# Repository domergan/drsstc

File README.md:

# Dual Resonance SSTC

My repo containing all my files and codes for my DRSSTC project. 

## Sources

- https://www.stevehv.4hv.org/DRSSTC.5.htm
- https://www.stevehv.4hv.org/new_driver.html
- https://www.f-legrand.fr/scidoc/docmml/sciphys/arduino/onduleur2/onduleur2.html

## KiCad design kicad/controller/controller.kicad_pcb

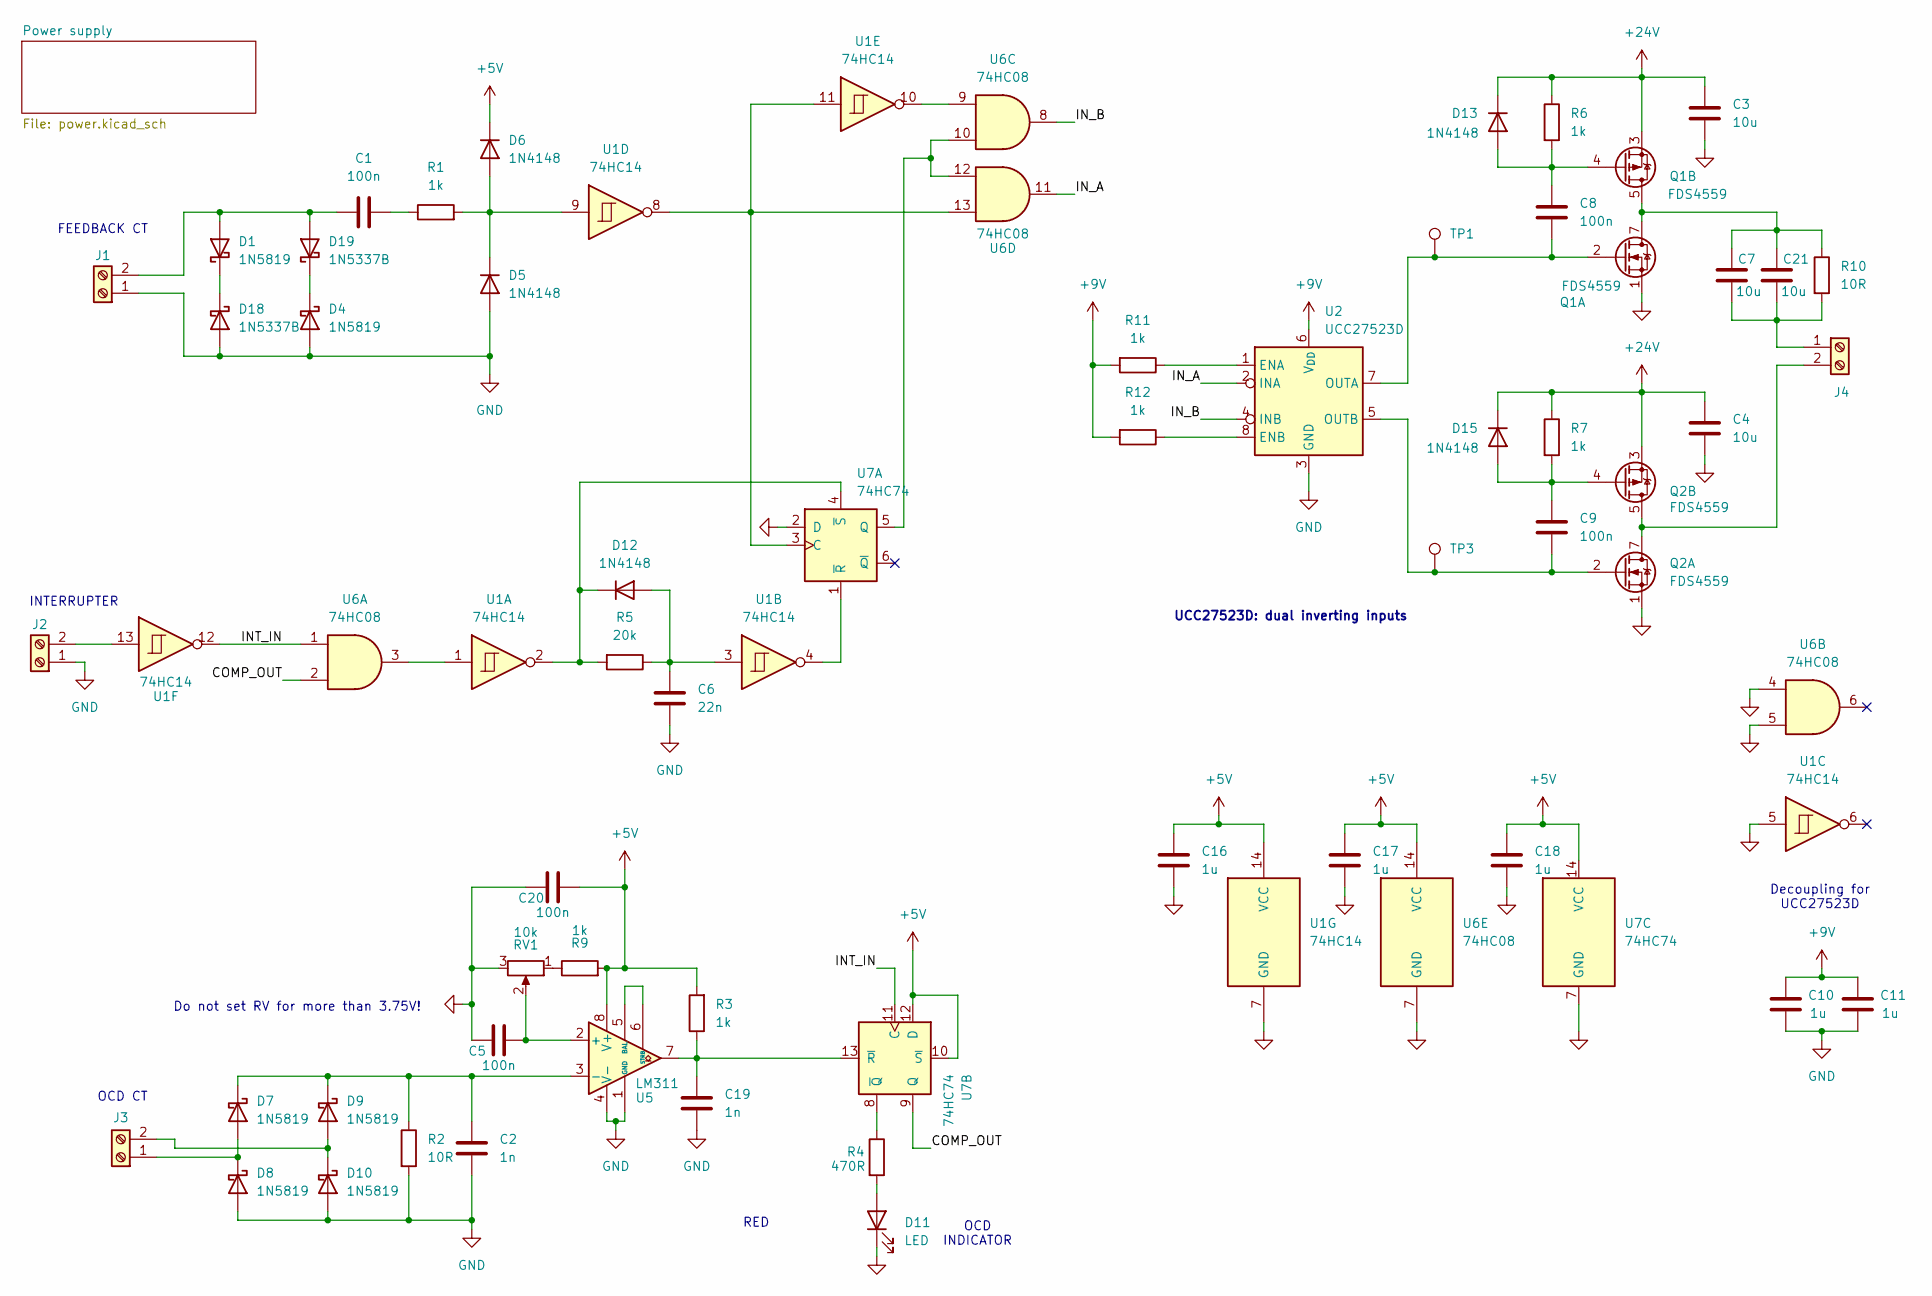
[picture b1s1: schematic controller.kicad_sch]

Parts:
C1, C5, C8, C9, C20: 100n; C_0805_2012Metric_Pad1.18x1.45mm_HandSolder
C2, C19: 1n; C_0805_2012Metric_Pad1.18x1.45mm_HandSolder
C3, C4, C7, C21: 10u; C_1206_3216Metric_Pad1.33x1.80mm_HandSolder
C6: 22n; C_0805_2012Metric_Pad1.18x1.45mm_HandSolder
C10, C11, C17, C18: 1u; C_1206_3216Metric_Pad1.33x1.80mm_HandSolder
C16: 1u; C_1206_3216Metric_Pad1.33x1.80mm_HandSolder; Voltage 10V
D1, D4, D7, D8, D9, D10: 1N5819; D_DO-41_SOD81_P2.54mm_Vertical_CathodeUp
D5, D6, D12, D13, D15: 1N4148; D_DO-35_SOD27_P2.54mm_Vertical_CathodeUp
D11: LED; LED_D3.0mm
D18, D19: 1N5337B; D_DO-201AD_P12.70mm_Horizontal
J1, J2, J3, J4: Screw_Terminal_01x02; TerminalBlock_MaiXu_MX126-5.0-02P_1x02_P5.00mm
Q1, Q2: FDS4559; SOIC-8_3.9x4.9mm_P1.27mm
R1, R3, R6, R7, R9, R11, R12: 1k; R_0805_2012Metric_Pad1.20x1.40mm_HandSolder
R2, R10: 10R; R_1206_3216Metric_Pad1.30x1.75mm_HandSolder
R4: 470R; R_0805_2012Metric_Pad1.20x1.40mm_HandSolder
R5: 20k; R_0805_2012Metric_Pad1.20x1.40mm_HandSolder
RV1: 10k; Potentiometer_Bourns_3266Y_Vertical
TP1, TP3: TestPoint; TestPoint_THTPad_D2.0mm_Drill1.0mm
U1: 74HC14; SOIC-14_3.9x8.7mm_P1.27mm
U2: UCC27523D; SOIC-8_3.9x4.9mm_P1.27mm
U5: LM311; SOIC-8_3.9x4.9mm_P1.27mm
U6: 74HC08; SOIC-14_3.9x8.7mm_P1.27mm
U7: 74HC74; SOIC-14_3.9x8.7mm_P1.27mm

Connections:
+5V: C16.2, C17.2, C18.2, C20.1, D6.1 (K), R3.2, R9.2, U1.14 (VCC), U5.8 (V+), U6.14 (VCC), U7.10 (~S), U7.12 (D), U7.14 (VCC); also elsewhere on the board
+9V: C10.2, C11.2, R11.2, R12.2, U2.6 (V_{DD}); also elsewhere on the board
+24V: C3.2, C4.2, D13.1 (K), D15.1 (K), Q1.3 (S2), Q2.3 (S2), R6.1, R7.1; also elsewhere on the board
/COMP_OUT: U6.2, U7.9 (Q)
/INT_IN: U1.12, U6.1, U7.11 (C)
/IN_A: U2.2 (INA), U6.11
/IN_B: U2.4 (INB), U6.8
GND: C2.1, C3.1, C4.1, C5.2, C6.2, C10.1, C11.1, C16.1, C17.1, C18.1, C19.2, C20.2, D4.2 (A), D5.2 (A), D8.2 (A), D10.2 (A), D11.1 (K), D18.2 (A), J1.1, J2.1, Q1.1 (S1), Q2.1 (S1), R2.2, RV1.3, U1.5, U1.7 (GND), U2.3 (GND), U5.1 (GND), U5.4 (V-), U6.4, U6.5, U6.7 (GND), U7.2 (D), U7.7 (GND); also elsewhere on the board
unnamed: C1.2, R1.1
unnamed: C7.2, C21.2, Q1.5 (D2), Q1.6 (D2), Q1.7 (D1), Q1.8 (D1), R10.1
unnamed: C1.1, D1.2 (A), D19.2 (A), J1.2
unnamed: D1.1 (K), D18.1 (K)
unnamed: D5.1 (K), D6.2 (A), R1.2, U1.9
unnamed: D7.2 (A), D8.1 (K), J3.1
unnamed: C2.2, D7.1 (K), D9.1 (K), R2.1, U5.3 (-)
unnamed: D9.2 (A), D10.1 (K), J3.2
unnamed: D11.2 (A), R4.2
unnamed: C6.1, D12.2 (A), R5.1, U1.3
unnamed: D12.1 (K), R5.2, U1.2, U7.4 (~S)
unnamed: C8.1, D13.2 (A), Q1.4 (G2), R6.2
unnamed: C9.1, D15.2 (A), Q2.4 (G2), R7.2
unnamed: D4.1 (K), D19.1 (K)
unnamed: J2.2, U1.13
unnamed: C7.1, C21.1, J4.1, R10.2
unnamed: J4.2, Q2.5 (D2), Q2.6 (D2), Q2.7 (D1), Q2.8 (D1)
unnamed: C8.2, Q1.2 (G1), TP1.1 (1_1), U2.7 (OUTA)
unnamed: C9.2, Q2.2 (G1), TP3.1 (1_1), U2.5 (OUTB)
unnamed: R9.1, RV1.1
unnamed: U1.1, U6.3
unnamed: U1.10, U6.9
unnamed: R11.1, U2.1 (ENA)
unnamed: R12.1, U2.8 (ENB)
unnamed: C5.1, RV1.2, U5.2 (+)
unnamed: U5.5 (BAL), U5.6 (STRB)
unnamed: U1.8, U1.11, U6.13, U7.3 (C)
unnamed: U6.10, U6.12, U7.5 (Q)
unnamed: U1.4, U7.1 (~R)
unnamed: R4.1, U7.8 (~Q)
unnamed: C19.1, R3.1, U5.7, U7.13 (~R)

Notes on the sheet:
OCD INDICATOR
Decoupling for UCC27523D
INTERRUPTER
UCC27523D: dual inverting inputs
FEEDBACK CT
OCD CT
Do not set RV for more than 3.75V!
RED

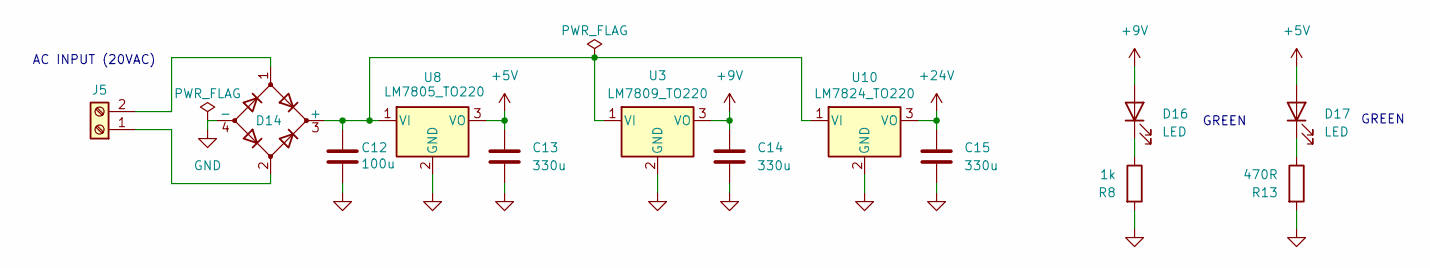
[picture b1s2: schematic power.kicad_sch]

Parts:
C12: 100u; CP_Radial_D10.0mm_P5.00mm
C13, C14, C15: 330u; CP_Radial_D10.0mm_P5.00mm
D14: TB210S; TB210S_ABS
D16, D17: LED; LED_D3.0mm
J5: Screw_Terminal_01x02; TerminalBlock_MaiXu_MX126-5.0-02P_1x02_P5.00mm
R8: 1k; R_0805_2012Metric_Pad1.20x1.40mm_HandSolder
R13: 470R; R_0805_2012Metric_Pad1.20x1.40mm_HandSolder
U3: LM7809_TO220; TO-220-3_Vertical
U8: LM7805_TO220; TO-220-3_Vertical
U10: LM7824_TO220; TO-220-3_Vertical

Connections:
+5V: C13.1, D17.2 (A), U8.3 (VO); also elsewhere on the board
+9V: C14.1, D16.2 (A), U3.3 (VO); also elsewhere on the board
+24V: C15.1, U10.3 (VO); also elsewhere on the board
GND: C12.2, C13.2, C14.2, C15.2, D14.4 (-), R8.2, R13.2, U3.2 (GND), U8.2 (GND), U10.2 (GND); also elsewhere on the board
unnamed: C12.1, D14.3 (+), U3.1 (VI), U8.1 (VI), U10.1 (VI)
unnamed: D16.1 (K), R8.1
unnamed: D17.1 (K), R13.1
unnamed: D14.2, J5.1
unnamed: D14.1, J5.2

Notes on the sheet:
AC INPUT (20VAC)
GREEN

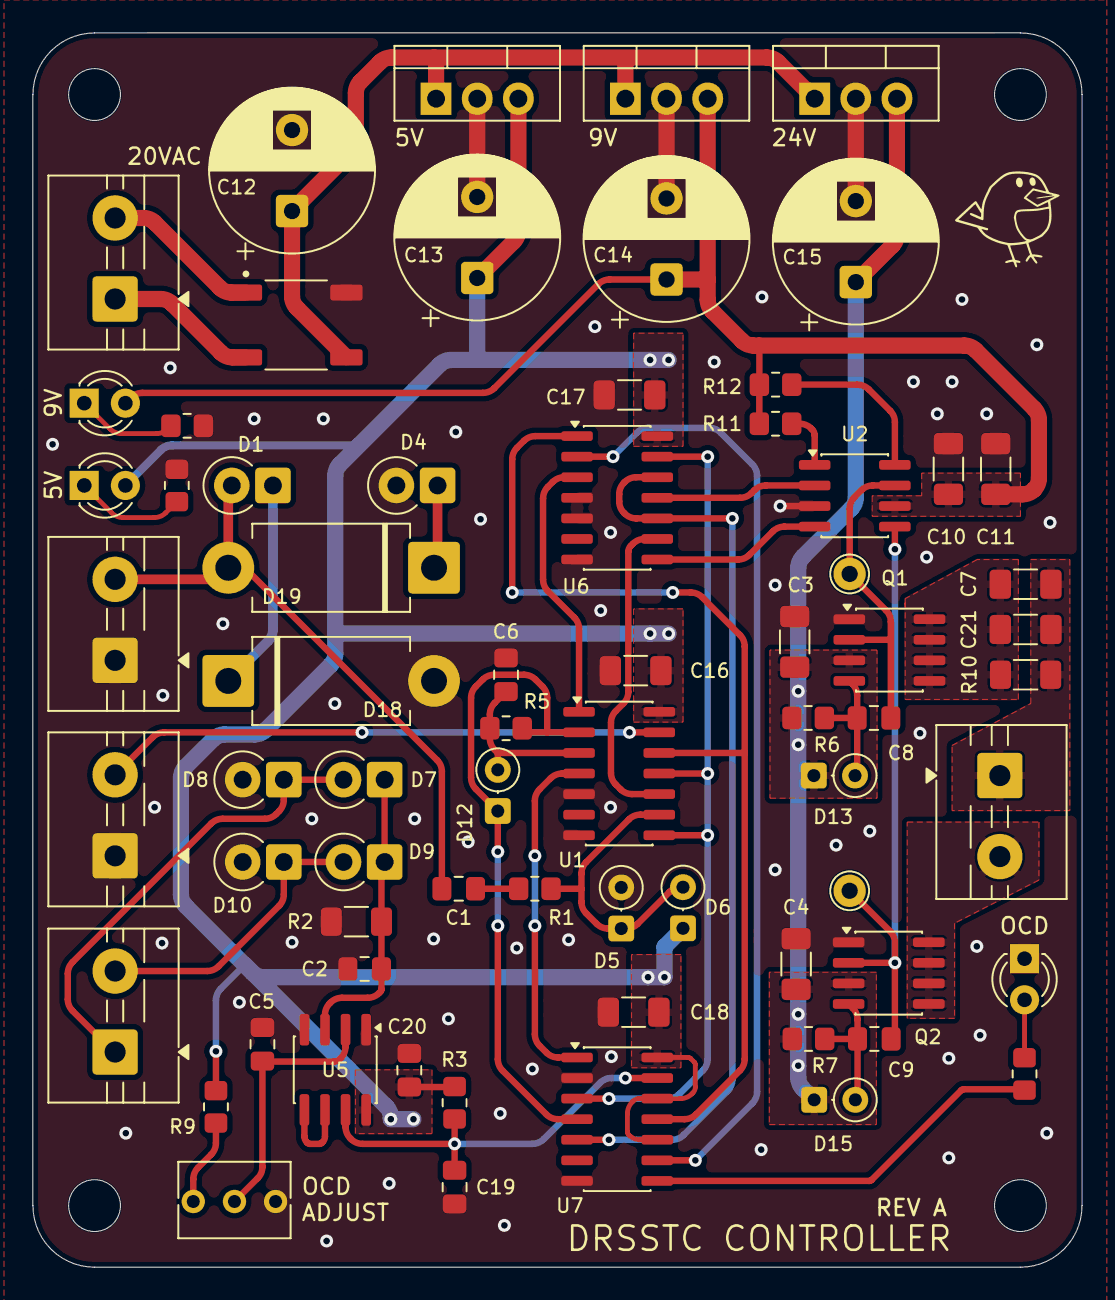
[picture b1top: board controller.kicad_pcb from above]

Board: 2 copper layers, 64.8 x 76.2 mm, 73 parts (0 on the bottom side), 44 nets.

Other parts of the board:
H1, H2, H3, H4: M3 / 3.2mm NPTH; MountingHole_3.2mm_M3
